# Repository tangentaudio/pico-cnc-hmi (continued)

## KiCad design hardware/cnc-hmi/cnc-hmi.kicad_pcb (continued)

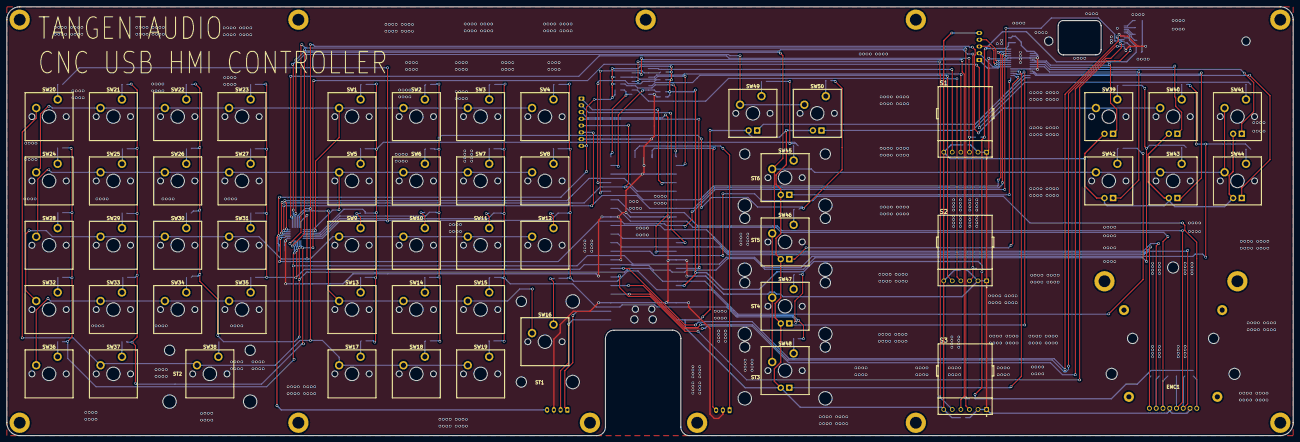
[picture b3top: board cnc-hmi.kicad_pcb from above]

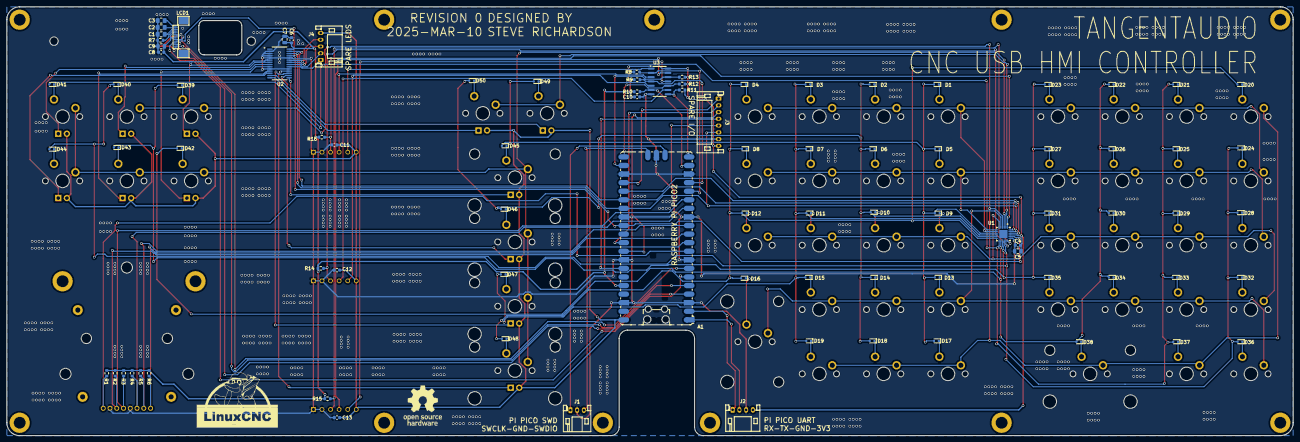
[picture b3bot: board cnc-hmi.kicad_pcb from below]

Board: 2 copper layers, 381.0 x 127.0 mm, 177 parts (90 on the bottom side), 125 nets.

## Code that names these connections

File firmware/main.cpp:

// PICO 2 GPIO MAP HW REV0
// =======================
// GPIO  0 - UART0 TX
// GPIO  1 - UART0 RX
// GPIO  2 - SPI0_SCK
// GPIO  3 - SPI0_DOUT
// GPIO  4 - LCD_A0
// GPIO  5 - SPI0_CS0
// GPIO  6 - JOG_A
// GPIO  7 - JOG_B
// GPIO  8 - SHUTTLE_0
// GPIO  9 - SHUTTLE_1
// GPIO 10 - SHUTTLE_2
// GPIO 11 - SHUTTLE_3
// GPIO 12 - ENC0_A
// GPIO 13 - ENC0_B
// GPIO 14 - ENC1_A
// GPIO 15 - ENC1_B
// GPIO 16 - ENC2_A
// GPIO 17 - ENC2_B
// GPIO 18 - SPARE
// GPIO 19 - /KEY_INT
// GPIO 20 - I2C0_SDA
// GPIO 21 - I2C0_SCL
// GPIO 22 - /PERIPH_RESET
// GPIO 26 - SPARE
// GPIO 27 - SPARE
// GPIO 28 - SPARE

#include <stdlib.h>
#include <stdio.h>
#include <string.h>

#include "bsp/board_api.h"
#include "tusb.h"
#include "encoder.hh"

/* Blink pattern
 * - 250 ms  : device not mounted
 * - 1000 ms : device mounted
 * - 2500 ms : device is suspended
 */
enum  {
  BLINK_NOT_MOUNTED = 250,
  BLINK_MOUNTED = 1000,
  BLINK_SUSPENDED = 2500,
};

static uint32_t blink_interval_ms = BLINK_NOT_MOUNTED;


void led_blinking_task(void);

union pkt_u {
  struct pkt_s {
    int knob1;
    int knob2;
    int knob3;
    uint8_t button1;
    uint8_t button2;
    uint8_t button3;
  } s;
  unsigned char buf[64];
} pkt;

int main(void)
{
  Encoder encoders;

  board_init();
  tud_init(BOARD_TUD_RHPORT);

  if (board_init_after_tusb) {
    board_init_after_tusb();
  }
  
  encoders.init();
  
  //gpio_init(ENCODER_1_PIN_BUTTON);
  //gpio_set_dir(ENCODER_1_PIN_BUTTON, GPIO_IN);
  //gpio_pull_up(ENCODER_1_PIN_BUTTON);
    //bool btn = gpio_get(ENCODER_1_PIN_BUTTON);
    //if ( btn != last_btn_1) {
    //  last_btn_1 = btn;
    //  update = true;
    //} 

  while (1)
  {

    tud_task();
    led_blinking_task();

    if (encoders.task()) {
      pkt.s.knob1 = encoders.value(0);
      pkt.s.knob2 = encoders.value(1);
      pkt.s.knob3 = encoders.value(2);
      pkt.s.button1 = 0;
      pkt.s.button2 = 0;
      pkt.s.button3 = 0;

      tud_hid_report(0, &pkt, sizeof(pkt));
    }
  }
}

//--------------------------------------------------------------------+
// Device callbacks
//--------------------------------------------------------------------+

// Invoked when device is mounted
void tud_mount_cb(void)
{
  blink_interval_ms = BLINK_MOUNTED;
}

// Invoked when device is unmounted
void tud_umount_cb(void)
{
  blink_interval_ms = BLINK_NOT_MOUNTED;
}

// Invoked when usb bus is suspended
// remote_wakeup_en : if host allow us  to perform remote wakeup
// Within 7ms, device must draw an average of current less than 2.5 mA from bus
void tud_suspend_cb(bool remote_wakeup_en)
{
  (void) remote_wakeup_en;
  blink_interval_ms = BLINK_SUSPENDED;
}

// Invoked when usb bus is resumed
void tud_resume_cb(void)
{
  blink_interval_ms = tud_mounted() ? BLINK_MOUNTED : BLINK_NOT_MOUNTED;
}

//--------------------------------------------------------------------+
// USB HID
//--------------------------------------------------------------------+

// Invoked when received GET_REPORT control request
// Application must fill buffer report's content and return its length.
// Return zero will cause the stack to STALL request
uint16_t tud_hid_get_report_cb(uint8_t itf, uint8_t report_id, hid_report_type_t report_type, uint8_t* buffer, uint16_t reqlen)
{
  // TODO not Implemented
  (void) itf;
  (void) report_id;
  (void) report_type;
  (void) buffer;
  (void) reqlen;

  return 0;
}

// Invoked when received SET_REPORT control request or
// received data on OUT endpoint ( Report ID = 0, Type = 0 )
void tud_hid_set_report_cb(uint8_t itf, uint8_t report_id, hid_report_type_t report_type, uint8_t const* buffer, uint16_t bufsize)
{
  // This example doesn't use multiple report and report ID
  (void) itf;
  (void) report_id;
  (void) report_type;

  // echo back anything we received from host
  // tud_hid_report(0, buffer, bufsize);
}

//--------------------------------------------------------------------+
// BLINKING TASK
//--------------------------------------------------------------------+
void led_blinking_task(void)
{
  static uint32_t start_ms = 0;
  static bool led_state = false;

  // Blink every interval ms
  if ( board_millis() - start_ms < blink_interval_ms) return; // not enough time
  start_ms += blink_interval_ms;

  board_led_write(led_state);
  led_state = 1 - led_state; // toggle
}

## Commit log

2025-02-14 initial
2025-02-26 hal side test
2025-03-04 reorg, adding hw design in progress
2025-03-08 hw wip
2025-03-10 Commit before rev0 release to fab
2025-03-10 rev0 to fab
2025-03-10 gitignore
2025-03-10 add rev0 renders
2025-03-14 add encoder led board
2025-03-15 prep for fab&assembly
2025-03-15 add wip USB/power module
2025-03-17 start rev0 hw test
2025-03-18 split encoder stuff off to class
2025-03-18 start of i2c
2025-03-19 first working tca8418 code
2025-03-19 polled-interrupt for tca8418
2025-03-19 shuttle control working
2025-03-19 add tlc59116 led driver support
2025-03-19 some cleanups, fix up tca8418 usage of i2c
2025-03-21 add SPI OLED SH1122 support
2025-03-22 fix signs of encoders
2025-03-23 WIP lvgl, just barely working now!wq
2025-03-23 wip before attempting 4bpp grayscale
2025-03-27 add ws2812 support
2025-03-28 encoder min/max settings
2025-03-28 full hw test demo
2025-03-29 make display/LVGL conditional, matrix cleanups
2025-03-29 integrating FreeRTOS
2025-03-29 reorg into task classes
2025-03-29 cleanups on matrix
2025-03-29 smart encoder value set
2025-03-29 reworking display to task, turned OFF for now
2025-03-30 remove mainline freertos kernel
2025-03-30 move to official Raspberry Pi port of FreeRTOS
2025-03-30 first working lvgl+freertos
2025-03-30 lvgl task work
2025-03-30 reorg source a bit
2025-03-31 more platform work, usb still not functional
2025-04-04 finally working usb. tinyusb debug level 3 breaks it!
2025-04-05 add HID keyboard+HID generic support
2025-04-05 testing integration w/linuxcnc
2025-04-07 hmi integration work
2025-04-09 wip bidir usb
2025-04-10 add blinking support to tlc59116 leds
2025-04-12 lcnc integration work
2025-04-12 integration
2026-04-20 picking the project back up with my buddy Claude.
2026-04-21 bunch of work improving knob/led ring and program control behaviors.
2026-04-21 project summary
2026-04-21 add homed state
2026-04-21 some hack cleanup fixes
2026-04-21 bump sdk and lvgl versions
2026-04-22 display tweaks
2026-04-22 keypad improvements
2026-04-22 several fixes
2026-04-22 new homing feature STOP+CYCLE START
2026-04-22 add probe basic sim
2026-04-22 PB integration doc
2026-04-23 feat: improve HMI step mode reliability, add auto-manual switching for jog, and refine HID interface detection
2026-04-24 rework program control logic from the ground up
2026-04-24 blink e-stop warning
2026-04-24 fix led swap
2026-04-24 make shift key dual function with space
2026-04-24 BOOTSEL firmware updater: - Add cmd byte (offset 14) to OUT packet; 0xB0 triggers reset_usb_boot(). - DISPLAY_CMD_BOOTSEL shows USB Boot message before MCU reset. - linuxcnc/update_firmware.py: full 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
2026-04-24 firmware versioning: auto-generated build numbers + HID feature report
    Build system:
    - gen_version.sh generates version_gen.h from git state on every build
    (major.minor from CMakeLists.txt, build=commit count, hash, dirty flag)
    - CMake custom target runs gen_version.sh before compilation
    - version_gen.h and build/ added to .gitignore
    Firmware:
2026-04-24 named LED constants, pause+cycle blink, SIGUSR2 updater
    Firmware:
    - Add LED_SINGLE_STEP/LED_PAUSE/LED_STOP/LED_CYCLE_START defines,
    replace all magic numbers in set_led_interp_state and elsewhere.
    - Pause state now blinks Pause + Cycle Start LEDs together.
    Host:
    - hmi.py: SIGUSR2 handler sends BOOTSEL reboot command on behalf of
2026-04-24 hmi_keymap.h, display status fix, updater robustness
    Firmware:
    - New hmi_keymap.h: named constants for all TCA8418 key codes
    (KEY_INCR_LG/MD/SM, KEY_AXIS_X/Y/Z, KEY_STOP, etc.) and TLC59116
    LED indices (LED_INCR_LG/MD/SM, LED_AXIS_X/Y/Z, etc.).
    Eliminates all magic numbers from main.cc.
    - Display status now respects step_mode in PAUSED and WAITING states:
2026-04-24 display: dedicated overlay panels, JetBrains Mono 48px, fix LVGL deadlock
    Refactor transient overlay system from single shared panel to dedicated
    per-type panels (jog, knob, select, bootsel). Each panel has its own
    pre-configured labels and fonts, eliminating runtime style/alignment
    reconfiguration.
    Visual changes:
    - JetBrains Mono SemiBold 48px (1bpp) for overlay letter and value
2026-04-24 display: 4bpp fonts, JetBrains Mono 20px status row, update docs
    - Switch overlay font back to 4bpp (smoother antialiasing on grayscale OLED)
    - Add JetBrains Mono 20px 4bpp for status row overrides (monospace alignment)
    - Remove space after colon in F:/R:/V: prefixes (tighter monospace layout)
    - Update doc/todo.md: mark jog overlay + LVGL deadlock as completed with
    full root-cause analysis; remove stale 'DISABLED, TODO revisit' section
2026-04-25 Replace Montserrat with build-time generated Roboto + FontAwesome fonts
    - Add fonts/generate_fonts.cmake: build-time font generation via lv_font_conv
    - Generate Roboto 14/18/20/28, JetBrains Mono 20/24/48, FA Solid 18/20/28
    - FA fallback baked into Roboto const structs via sed post-processing (stays in flash)
    - Override LV_SYMBOL_USB to FA7 plug icon (0xF1E6), FA5 USB (0xF287) absent in FA7
    - Disable all built-in LV_FONT_MONTSERRAT_* (~100KB flash savings)
    - Set LV_FONT_DEFAULT to generated roboto_14
2026-04-25 Add segmented speed bar to jog overlay for shuttle speed indication
    - 14 pre-created rectangle segments (7 left/reverse, 7 right/forward)
    - Positioned at bottom of jog overlay panel, text shifted up 5px
    - Brightness ramps from dim gray (level 1) to full white (level 7)
    - Driven by raw shuttle encoder value (-7..+7) passed through jog_overlay_t
    - Hidden during incremental jog (MPG wheel) — only shown for continuous/shuttle
2026-04-25 Add incremental jog direction flash on speed bar
    - MPG wheel clicks flash all 7 segments in the jog direction for 100ms
    - Direction computed from encoder delta (+1/-1)
    - Continuous shuttle retains static bar display unchanged
    - speed_level field added to jog_overlay_t for both modes
2026-04-25 Move shuttle speed lookup from firmware to hmi.py
    - Firmware now sends raw shuttle position (-7..+7) over USB
    - Removed hardcoded speed lookup table from task_encoder.cc
    - hmi.py applies configurable speed table: 0.5, 1, 2, 5, 10, 25, 60 IPM
    - halui.axis.jog-speed takes units/min (IPM), values sent directly
    - Speeds configurable via [DISPLAY] HMI_SHUTTLE_SPEEDS in INI file
    (7 comma-separated values in IPM, e.g. '0.5,1,2,5,10,25,60')
2026-04-25 Replace wait screen with Pico CNC HMI title + version
    - Removed USB plug icon and 'Waiting for connection...' text
    - Shows 'Pico CNC HMI' (roboto_20) centered with version below (roboto_14)
    - Both labels vertically centered on the 64px display
2026-04-25 jog speeds for testing
2026-04-25 Scope version dirty check to firmware/ only
    Skip submodule and non-firmware changes (e.g. linuxcnc/*.var)
    when determining the +dirty suffix for the firmware version string.
